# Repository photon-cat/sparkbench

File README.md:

# SparkBench

**All-in-one hardware development platform powered by Claude Opus 4.6**

SparkBench combines what normally takes 5 separate tools into one browser-based workbench: a code editor, circuit simulator, MCU emulator, EDA/PCB designer, and an AI engineering partner — all working together so you can go from idea to tested hardware in minutes instead of days.

## What It Does

- **Prompt-to-Circuit**: Describe what you want to build. Sparky (the AI agent) designs the schematic, writes the firmware, and presents a diff for your review.
- **Cycle-Accurate Simulation**: Run your Arduino code on an AVR emulator with 13+ simulated components (LEDs, servos, encoders, displays, sensors, shift registers).
- **KiCAD-Compatible PCB Editor**: Our custom-built PCB editor reads and writes native `.kicad_pcb` files. Built as a fork of KiCanvas with a full editing layer — component drag-and-drop, footprint rotation/flip, board outline editing (rectangle or SVG import), interactive trace routing, zone drawing, layer management, ratsnest display, courtyard DRC, undo/redo, and a 3D board preview. Everything stays in the KiCAD s-expression format so you can open your boards directly in KiCAD.
- **DeepPCB Autorouter Integration**: One-click AI-powered autorouting via [DeepPCB](https://deeppcb.ai). Send your board to DeepPCB's cloud autorouter directly from the PCB editor or let Sparky handle it conversationally. Extracts constraints, validates, runs placement and routing, and pulls back the routed board — all streamed with live progress.
- **Headless CI Testing**: Write YAML test scenarios and run them against the simulator — no hardware needed. AI-powered fuzz testing presses all the buttons and reports what broke.
- **Full-Context AI Agent**: Sparky has access to your entire project (schematic, code, PCB, libraries) and can debug, refactor, add features, route your PCB, or explain your circuit.

## Tech Stack

- **Frontend**: Next.js 16, React 19, Monaco Editor, Three.js (3D PCB viewer)
- **Simulation**: [avr8js](https://github.com/niclas-niclas/avr8js) (AVR emulator), [@wokwi/elements](https://github.com/niclas-niclas/wokwi-elements) (component visuals)
- **PCB Editor**: Custom KiCanvas fork with full editing — reads/writes `.kicad_pcb` s-expression format natively. Clipper2 for polygon math, WebGL2 rendering.
- **Autorouter**: [DeepPCB](https://deeppcb.ai) MCP integration — AI-powered PCB routing via SSE transport
- **AI**: Claude Opus 4.6 via [@anthropic-ai/claude-agent-sdk](https://www.npmjs.com/package/@anthropic-ai/claude-agent-sdk), custom MCP server for simulation control, DeepPCB MCP server for autorouting
- **Build**: PlatformIO (AVR compilation), runs entirely in the browser except compilation

## Architecture

```
┌─────────────────────────────────────────────────────────────┐
│  SparkBench Web                                             │
│  ┌──────────┐  ┌──────────────┐  ┌───────────────────────┐  │
│  │  Monaco   │  │  Diagram     │  │  Sparky Chat          │  │
│  │  Editor   │  │  Canvas      │  │  (Claude Opus 4.6)    │  │
│  │          │  │  + Wires     │  │  Agent SDK + MCP      │  │
│  └──────────┘  └──────────────┘  └───────────────────────┘  │
│  ┌──────────┐  ┌──────────────┐  ┌───────────────────────┐  │
│  │  Serial   │  │  PCB Editor  │  │  3D Board Viewer      │  │
│  │  Monitor  │  │  (KiCanvas   │  │  (Three.js)           │  │
│  │          │  │   fork)      │  │                       │  │
│  └──────────┘  └──────────────┘  └───────────────────────┘  │
│                                                             │
│  ┌─────────────────────────────────────────────────────────┐│
│  │  AVR Simulation Engine                                  ││
│  │  avr8js + I2C bus + SPI + USART + ADC + Timer/PWM      ││
│  │  Wire components: LED, servo, encoder, SSD1306, ...     ││
│  └─────────────────────────────────────────────────────────┘│
│                                                             │
│  ┌─────────────────────────────────────────────────────────┐│
│  │  DeepPCB Autorouter (via MCP SSE)                       ││
│  │  Extract constraints → Validate → Place → Route → Done  ││
│  └─────────────────────────────────────────────────────────┘│
└─────────────────────────────────────────────────────────────┘

┌─────────────────────────────────────────────────────────────┐
│  SparkBench CI                                              │
│  YAML scenarios → PlatformIO compile → headless AVR sim     │
│  set-control, wait-serial, expect-serial, expect-display    │
└─────────────────────────────────────────────────────────────┘
```

## PCB Editor

The PCB editor is a custom-built KiCAD-compatible editor, not a wrapper around existing tools. It reads and writes `.kicad_pcb` files natively using our own s-expression parser/serializer.

### Features

- **Component placement** — Click-to-select via pad proximity, drag with crosshair preview, grid snapping (0.5mm)
- **Footprint editing** — Rotate (R), flip front/back copper (F), delete, courtyard overlap detection
- **Board outline** — Set rectangle dimensions or upload custom SVG outlines, converted to KiCAD Edge.Cuts
- **Trace routing** — Interactive routing with orthogonal and 45° diagonal modes, via insertion, layer switching
- **Zone drawing** — Copper pour zones with net auto-detection from pad clicks
- **Layer management** — Full KiCAD layer stack (F.Cu, B.Cu, silkscreen, masks, etc.) with visibility toggles and highlighting
- **Ratsnest** — Displays unrouted connections as airline wires
- **Undo/redo** — 50-level snapshot-based undo stack
- **3D preview** — Three.js-based 3D board viewer with component models
- **Export** — Download `.kicad_pcb` files that open directly in KiCAD

### DeepPCB Autorouter

The PCB editor integrates with [DeepPCB](https://deeppcb.ai) for AI-powered autorouting. Two ways to use it:

**From the UI:** Click "Route with DeepPCB" in the PCB editor's right panel. The board is sent to DeepPCB's cloud autorouter, progress streams back in real-time, and the routed board is loaded back into the editor automatically.

**From Sparky:** Ask the AI agent to route your board (e.g., "route my PCB with DeepPCB"). Sparky uses DeepPCB's MCP tools directly — extracting constraints, validating, running placement/routing, and saving the result.

The autorouter workflow:
1. **Extract constraints** from the `.kicad_pcb` file
2. **Validate constraints** for correctness
3. **Run placement** — AI-optimized component positioning
4. **Run routing** — AI-powered trace routing
5. **Monitor progress** — live status updates streamed to the UI
6. **Retrieve result** — best routed board saved back to the project

## Getting Started

### Prerequisites

- Node.js 20+
- [PlatformIO Core](https://docs.platformio.org/en/latest/core/installation.html) (for compilation)
- Anthropic API key (for Sparky agent)
- DeepPCB API key (optional, for autorouting)

### Setup

```bash
git clone https://github.com/photon-cat/sparkbench.git
cd sparkbench
npm install
cp .env.example .env.local
# Edit .env.local with your keys:
#   ANTHROPIC_API_KEY=sk-ant-...
#   DEEPPCB_API_KEY=...          (optional, enables autorouter)
npm run dev
```

Open [http://localhost:3000](http://localhost:3000) to start building.

### SparkBench CLI

SparkBench includes a command-line tool for running tests and AI-powered security fuzzing directly from your terminal.

```bash
# Run it via npm
npm run sparkbench -- help

# Or directly with tsx
npx tsx scripts/sparkbench-cli.ts help
```

#### Commands

```
sparkbench test <project> [--scenario <file>]   Run a YAML test scenario
sparkbench fuzz <project>                       AI security fuzzer (SparkyFuzzer)
sparkbench list                                 List all projects
sparkbench help                                 Show help
```

#### Running Tests

Compile firmware with PlatformIO, then run a YAML test scenario against the headless AVR simulator:

```bash
npm run sparkbench -- test combo-safe
```

Test scenarios support: `delay`, `set-control` (buttons, encoders, pots, sensors), `send-serial`, `wait-serial`, `expect-serial`, `expect-display`, and `clear-serial`.

#### SparkyFuzzer (AI Security Auditor)

SparkyFuzzer uses Claude Opus 4.6 to analyze your firmware source code, identify security vulnerabilities, and generate exploit scenarios that run against the headless simulator to prove exploitability.

```bash
# Set your API key
export ANTHROPIC_API_KEY=sk-ant-...

# Fuzz the combo-safe demo (has 3 intentional vulnerabilities)
npm run sparkbench -- fuzz combo-safe
```

The fuzzer:
1. Sends your `sketch.ino` and `diagram.json` to Claude Opus 4.6
2. Claude identifies potential vulnerabilities (timing side-channels, integer overflows, backdoors, buffer overflows, etc.)
3. Claude generates YAML test scenarios that exploit each vulnerability
4. SparkBench runs each scenario headlessly against the AVR simulator
5. Claude analyzes the results and writes a security report

Reports are saved to `projects/<slug>/fuzzer-report/`.

## Simulated Components

| Component | Simulation |
|-----------|-----------|
| LED | GPIO state → visual on/off |
| Pushbutton | INPUT_PULLUP, interactive click |
| Potentiometer | ADC voltage via slider |
| Servo | PWM pulse width → angle display |
| Rotary Encoder (KY-040) | Quadrature CLK/DT signals |
| SSD1306 OLED | Full I2C controller, pixel display |
| 74HC595 | Serial-in/parallel-out, daisy chain |
| 74HC165 | Parallel-in/serial-out |
| DHT22 | One-wire temp/humidity with sliders |
| MPU6050 | I2C accel/gyro with sliders |
| 7-Segment Display | Via HC595 outputs |
| Buzzer | GPIO state detection |
| Slide Switch | Toggle state |

## Project Structure

```
sparkbench/
├── app/                    # Next.js app router
│   ├── api/chat/           # Sparky agent endpoint (Agent SDK)
│   ├── api/deeppcb/        # DeepPCB autorouter endpoint
│   ├── api/projects/       # Project CRUD + build API
│   └── projects/[slug]/    # Workbench page
├── components/             # React components
│   ├── DiagramCanvas.tsx   # Schematic editor with wiring
│   ├── SparkyChat.tsx      # AI chat panel with diff review
│   ├── KiPCBEditor.tsx     # PCB editor (KiCanvas fork)
│   ├── KiPCBCanvas.tsx     # WebGL2 board renderer
│   ├── KiPCBToolPalette.tsx # PCB tool sidebar
│   ├── KiPCBLayerPanel.tsx # Layer visibility/selection
│   ├── PCB3DViewer.tsx     # 3D board viewer (Three.js)
│   └── SimulationPanel.tsx # Simulation controls + tabs
├── hooks/                  # React hooks
│   ├── useKiPCBDrag.ts     # Footprint drag + courtyard DRC
│   ├── useKiPCBRouting.ts  # Interactive trace routing
│   ├── useKiPCBZoneDraw.ts # Copper zone drawing
│   └── useKiPCBBoardOutline.ts # Board outline editing
├── lib/                    # Core logic
│   ├── avr-runner.ts       # AVR emulator wrapper
│   ├── wire-components.ts  # Part simulation bindings
│   ├── scenario-runner.ts  # CI test runner
│   ├── sexpr-mutate.ts     # KiCAD s-expression tree manipulation
│   ├── sexpr-serializer.ts # S-expression → .kicad_pcb text
│   ├── deeppcb-client.ts   # DeepPCB MCP client wrapper
│   ├── pcb-parser.ts       # Schematic → PCB conversion
│   └── sparky-prompts.ts   # Sparky system prompt
├── vendor/kicanvas/        # KiCanvas fork (WebGL2 PCB renderer)
├── scripts/
│   ├── sparkbench-cli.ts   # CLI entry point (sparkbench command)
│   ├── run-scenario.ts     # Headless test runner
│   └── sparky-fuzzer.ts    # AI security fuzzer (SparkyFuzzer)
├── projects/               # User projects (diagram.json + sketch.ino)
└── _build/                 # PlatformIO build directory
```

## Hackathon Track

**Problem Statement Two: Break the Barriers** — Hardware development requires expensive tools (Altium, oscilloscopes), deep expertise (PCB layout, embedded C), and physical prototyping cycles. SparkBench puts the full hardware development workflow in everyone's hands with an AI partner that understands embedded systems.

## Built With

Built entirely during the [Claude Code Hackathon](https://cv.inc/e/claude-code-hackathon) using Claude Opus 4.6 and Claude Code.

## Team

- **photoncat** (Jacob Armstrong)

## License

MIT

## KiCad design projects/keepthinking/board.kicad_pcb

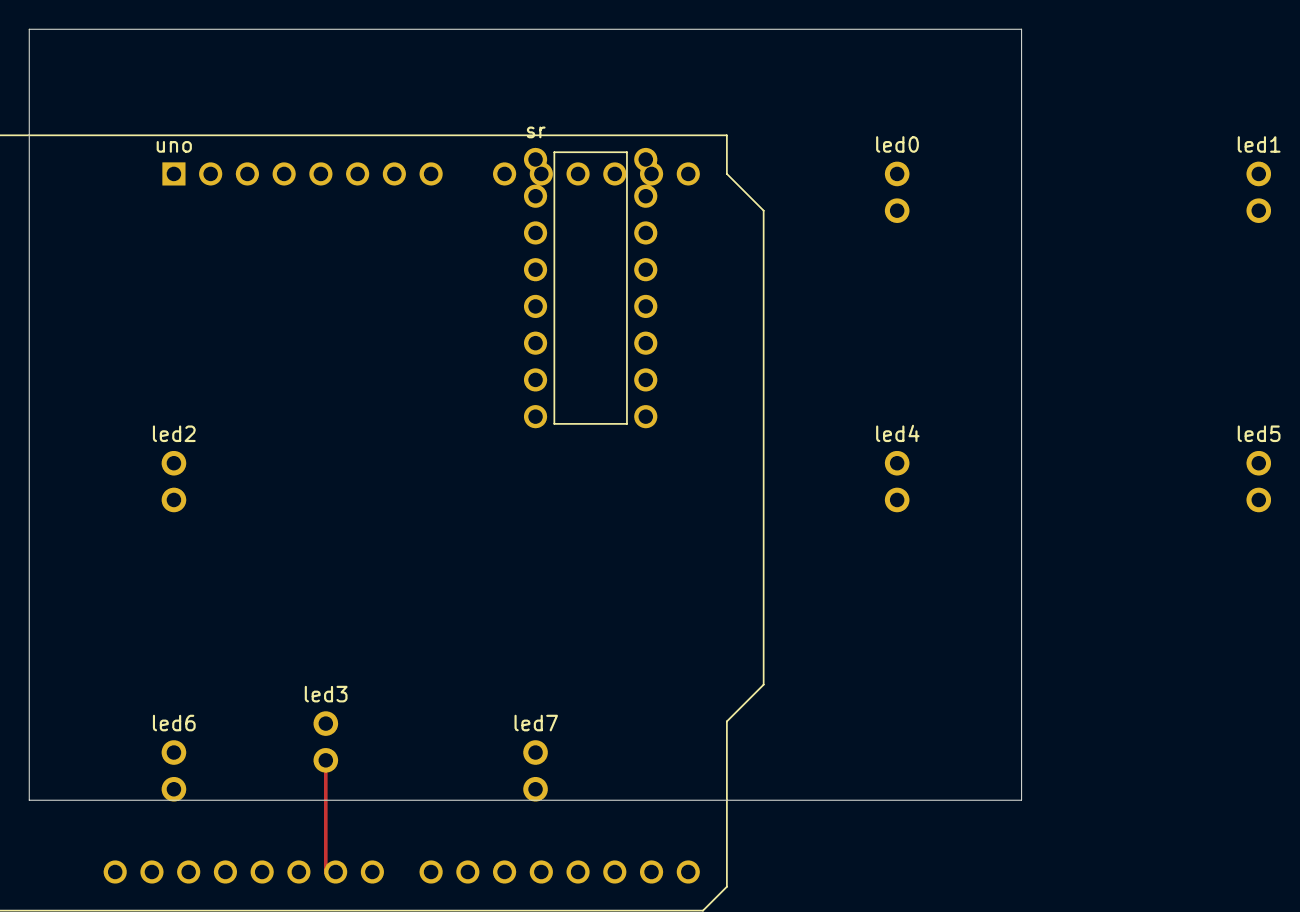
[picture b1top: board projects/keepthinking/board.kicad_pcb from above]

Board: 2 copper layers, 68.6 x 53.3 mm, 10 parts (0 on the bottom side), 15 nets.

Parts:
led0, led1, led2, led3, led4, led5, led6, led7: LED-THT-3mm
sr: DIP-16
uno: Arduino-Uno-Shield

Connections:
Net-1: sr.sr:14, uno.uno:4
Net-2: sr.sr:11, uno.uno:3
Net-3: sr.sr:12, uno.uno:2
Net-4: sr.sr:10, sr.sr:16, uno.uno:5V
Net-5: sr.sr:8, sr.sr:13, uno.uno:GND.1
Net-6: led0.led0:1, sr.sr:15
Net-7: led1.led1:1, sr.sr:1
Net-8: led2.led2:1, sr.sr:2
Net-9: led3.led3:1, sr.sr:3
Net-10: led4.led4:1, sr.sr:4
Net-11: led5.led5:1, sr.sr:5
Net-12: led6.led6:1, sr.sr:6
Net-13: led7.led7:1, sr.sr:7
Net-14: led0.led0:2, led1.led1:2, led2.led2:2, led3.led3:2, uno.uno:GND.2
Net-15: led4.led4:2, led5.led5:2, led6.led6:2, led7.led7:2, uno.uno:GND.3

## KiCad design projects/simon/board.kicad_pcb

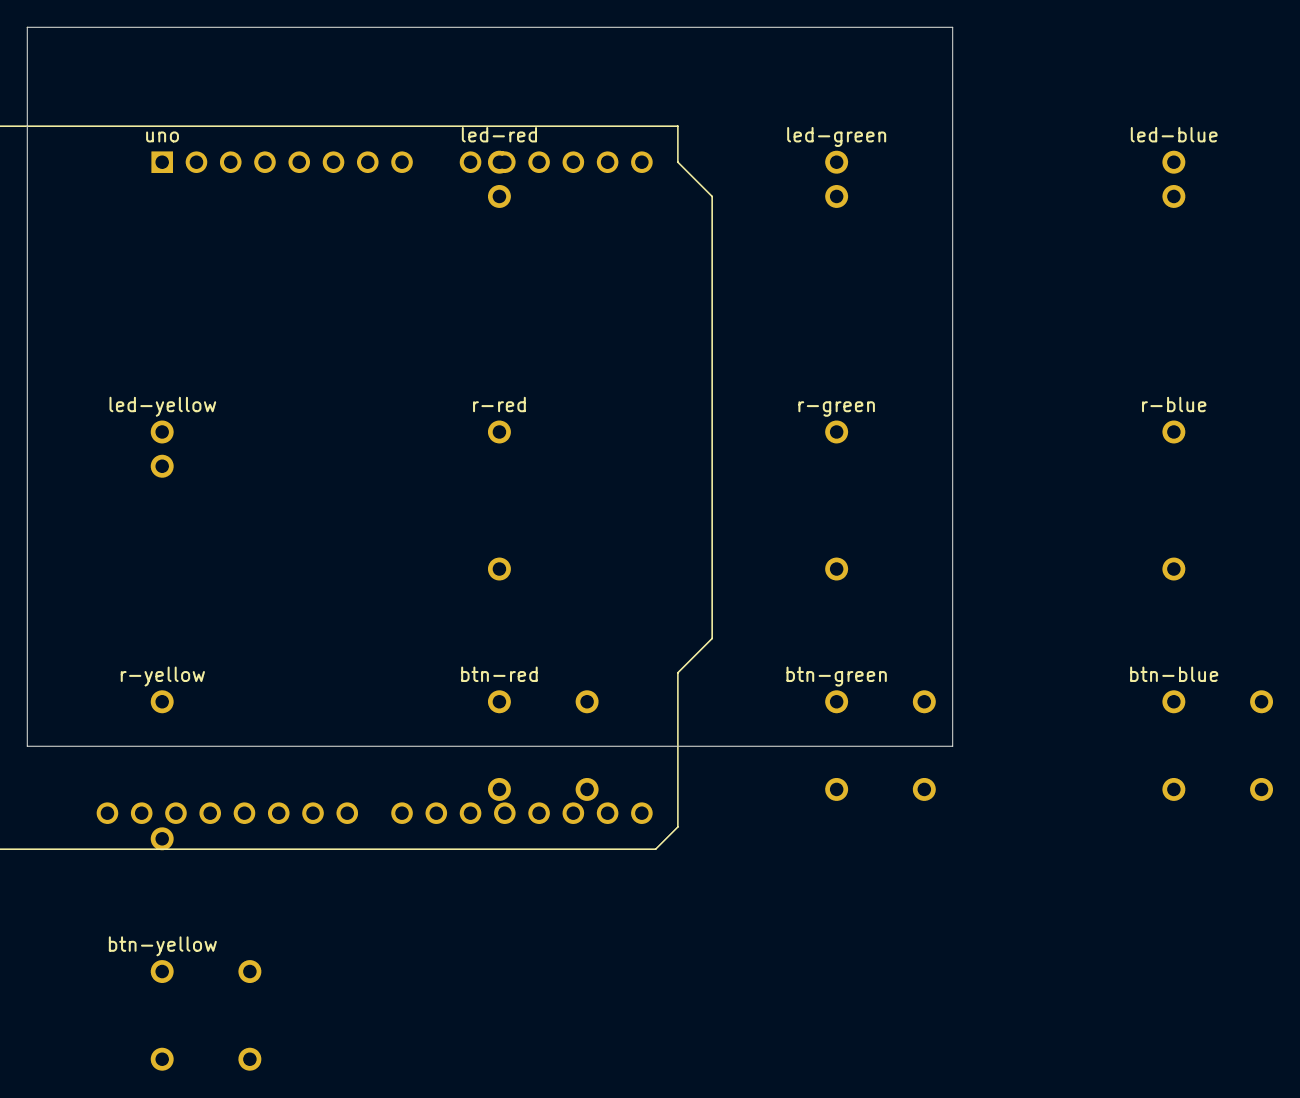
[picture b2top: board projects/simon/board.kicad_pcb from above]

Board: 2 copper layers, 68.6 x 53.3 mm, 13 parts (0 on the bottom side), 14 nets, no tracks yet.

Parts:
btn-blue: SW-THT-6mm
btn-green: SW-THT-6mm
btn-red: SW-THT-6mm
btn-yellow: SW-THT-6mm
led-blue: LED-THT-3mm
led-green: LED-THT-3mm
led-red: LED-THT-3mm
led-yellow: LED-THT-3mm
r-blue: 220; Axial-0.4in
r-green: 220; Axial-0.4in
r-red: 220; Axial-0.4in
r-yellow: 220; Axial-0.4in
uno: Arduino-Uno-Shield

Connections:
Net-1: r-red.r-red:1, uno.uno:12
Net-2: led-red.led-red:1, r-red.r-red:2
Net-3: btn-green.btn-green:1, btn-red.btn-red:1, led-green.led-green:2, led-red.led-red:2, uno.uno:GND.1
Net-4: r-green.r-green:1, uno.uno:11
Net-5: led-green.led-green:1, r-green.r-green:2
Net-6: r-blue.r-blue:1, uno.uno:10
Net-7: led-blue.led-blue:1, r-blue.r-blue:2
Net-8: btn-blue.btn-blue:4, btn-yellow.btn-yellow:4, led-blue.led-blue:2, led-yellow.led-yellow:2, uno.uno:GND.2
Net-9: r-yellow.r-yellow:1, uno.uno:9
Net-10: led-yellow.led-yellow:1, r-yellow.r-yellow:2
Net-11: btn-red.btn-red:4, uno.uno:5
Net-12: btn-green.btn-green:4, uno.uno:4
Net-13: btn-blue.btn-blue:1, uno.uno:3
Net-14: btn-yellow.btn-yellow:1, uno.uno:2

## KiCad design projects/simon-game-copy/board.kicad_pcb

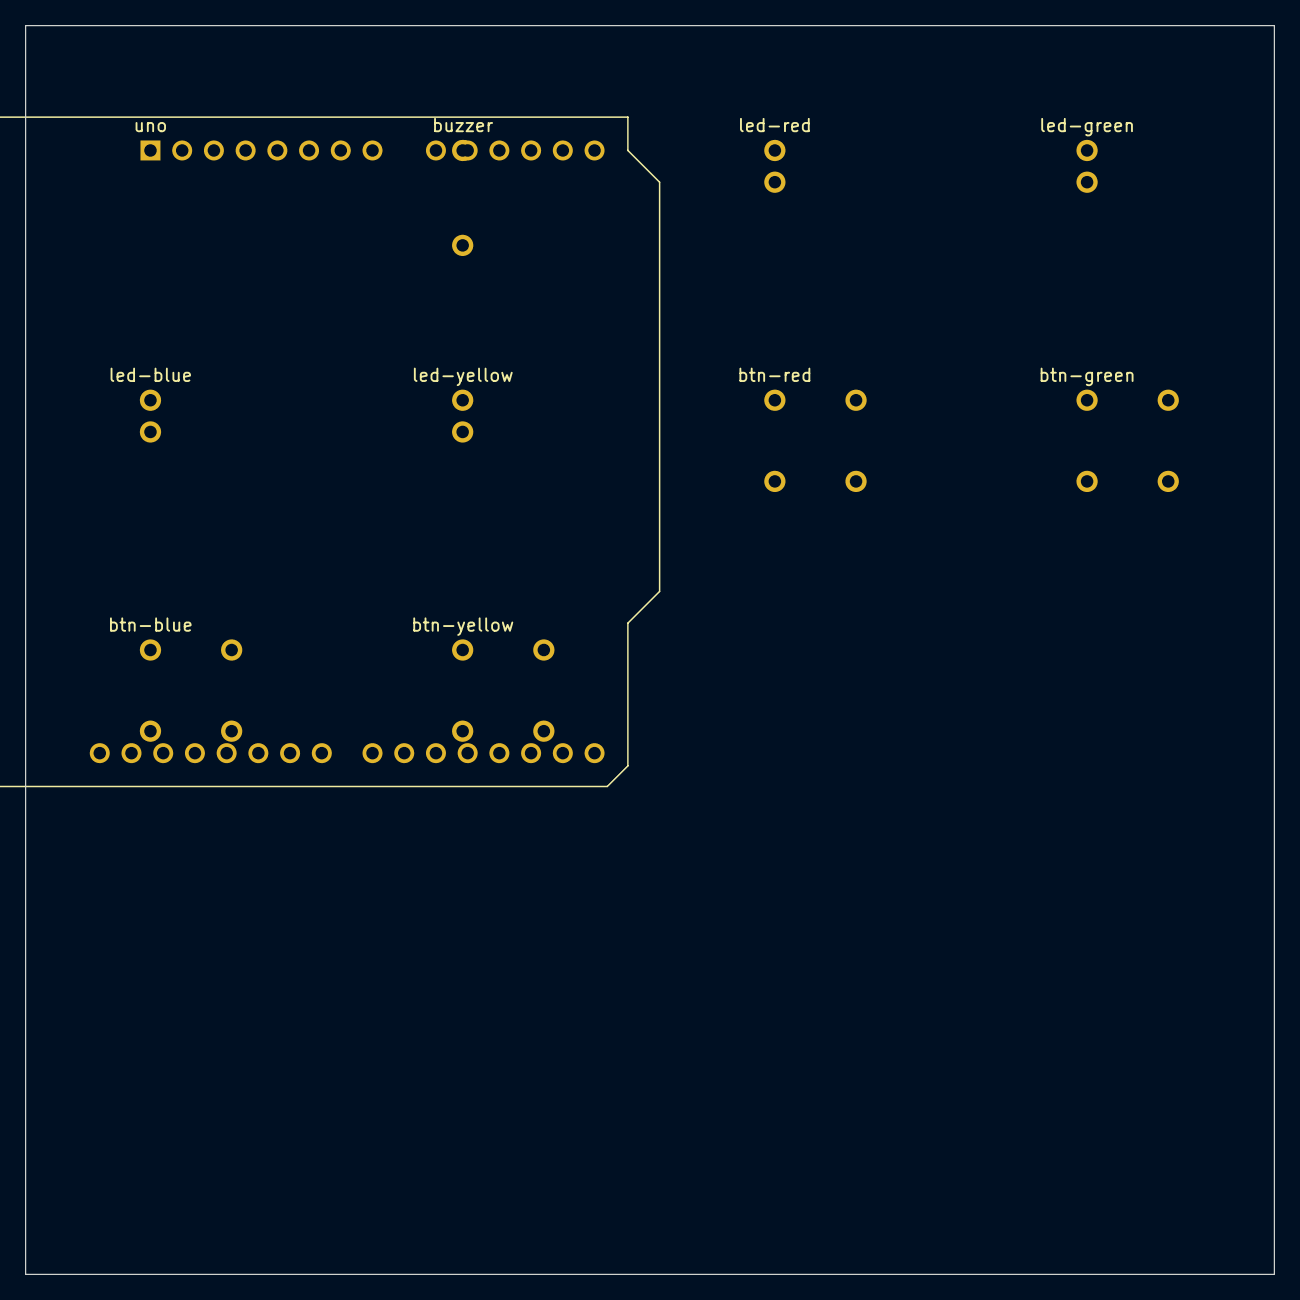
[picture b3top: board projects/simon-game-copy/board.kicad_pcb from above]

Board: 2 copper layers, 100.0 x 100.0 mm, 10 parts (0 on the bottom side), 10 nets, no tracks yet.

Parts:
btn-blue: SW-THT-6mm
btn-green: SW-THT-6mm
btn-red: SW-THT-6mm
btn-yellow: SW-THT-6mm
buzzer: Buzzer-12mm
led-blue: LED-THT-3mm
led-green: LED-THT-3mm
led-red: LED-THT-3mm
led-yellow: LED-THT-3mm
uno: Arduino-Uno-Shield

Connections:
Net-1: btn-blue.btn-blue:4, btn-green.btn-green:1, btn-red.btn-red:1, btn-yellow.btn-yellow:4, buzzer.buzzer:1, led-blue.led-blue:2, led-green.led-green:2, led-red.led-red:2, led-yellow.led-yellow:2, uno.uno:GND.1
Net-2: btn-yellow.btn-yellow:1, uno.uno:2
Net-3: btn-blue.btn-blue:1, uno.uno:3
Net-4: btn-green.btn-green:4, uno.uno:4
Net-5: btn-red.btn-red:4, uno.uno:5
Net-6: buzzer.buzzer:2, uno.uno:8
Net-7: led-yellow.led-yellow:1, uno.uno:9
Net-8: led-blue.led-blue:1, uno.uno:10
Net-9: led-green.led-green:1, uno.uno:11
Net-10: led-red.led-red:1, uno.uno:12

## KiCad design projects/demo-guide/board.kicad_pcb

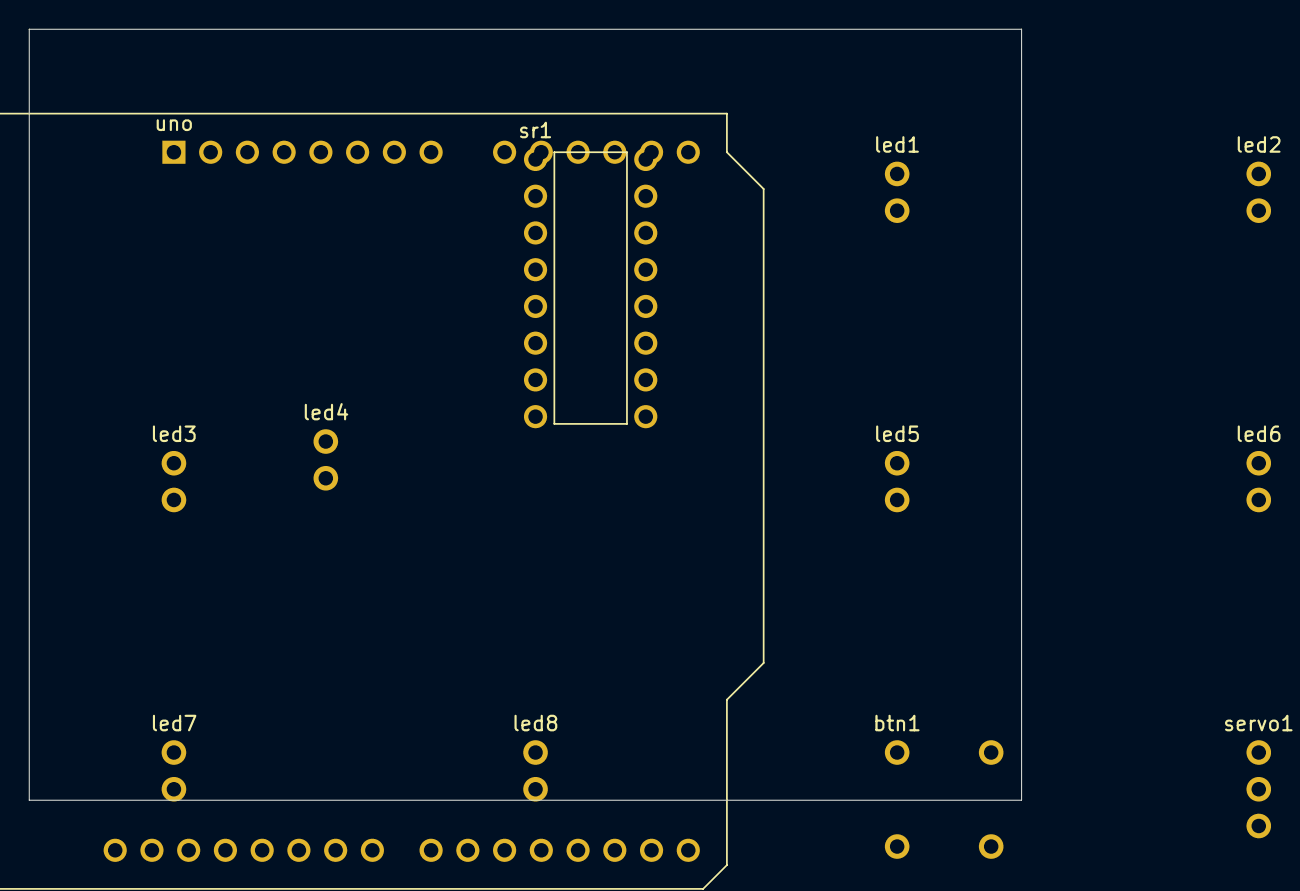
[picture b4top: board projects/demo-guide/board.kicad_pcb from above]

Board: 2 copper layers, 68.6 x 53.3 mm, 12 parts (0 on the bottom side), 17 nets, no tracks yet.

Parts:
btn1: SW-THT-6mm
led1, led2, led3, led4, led5, led6, led7, led8: LED-THT-3mm
servo1: Header-1x3
sr1: DIP-16
uno: Arduino-Uno-Shield

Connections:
Net-1: sr1.sr1:14, uno.uno:2
Net-2: sr1.sr1:11, uno.uno:3
Net-3: sr1.sr1:12, uno.uno:4
Net-4: servo1.servo1:2, sr1.sr1:16, uno.uno:5V
Net-5: led1.led1:2, led2.led2:2, led3.led3:2, led4.led4:2, led5.led5:2, led6.led6:2, led7.led7:2, led8.led8:2, sr1.sr1:8, sr1.sr1:13, uno.uno:GND.1
Net-6: led1.led1:1, sr1.sr1:15
Net-7: led2.led2:1, sr1.sr1:1
Net-8: led3.led3:1, sr1.sr1:2
Net-9: led4.led4:1, sr1.sr1:3
Net-10: led5.led5:1, sr1.sr1:4
Net-11: led6.led6:1, sr1.sr1:5
Net-12: led7.led7:1, sr1.sr1:6
Net-13: led8.led8:1, sr1.sr1:7
Net-14: btn1.btn1:4, uno.uno:5
Net-15: btn1.btn1:1, uno.uno:GND.2
Net-17: servo1.servo1:1, uno.uno:GND.3
Net-18: servo1.servo1:3, uno.uno:9

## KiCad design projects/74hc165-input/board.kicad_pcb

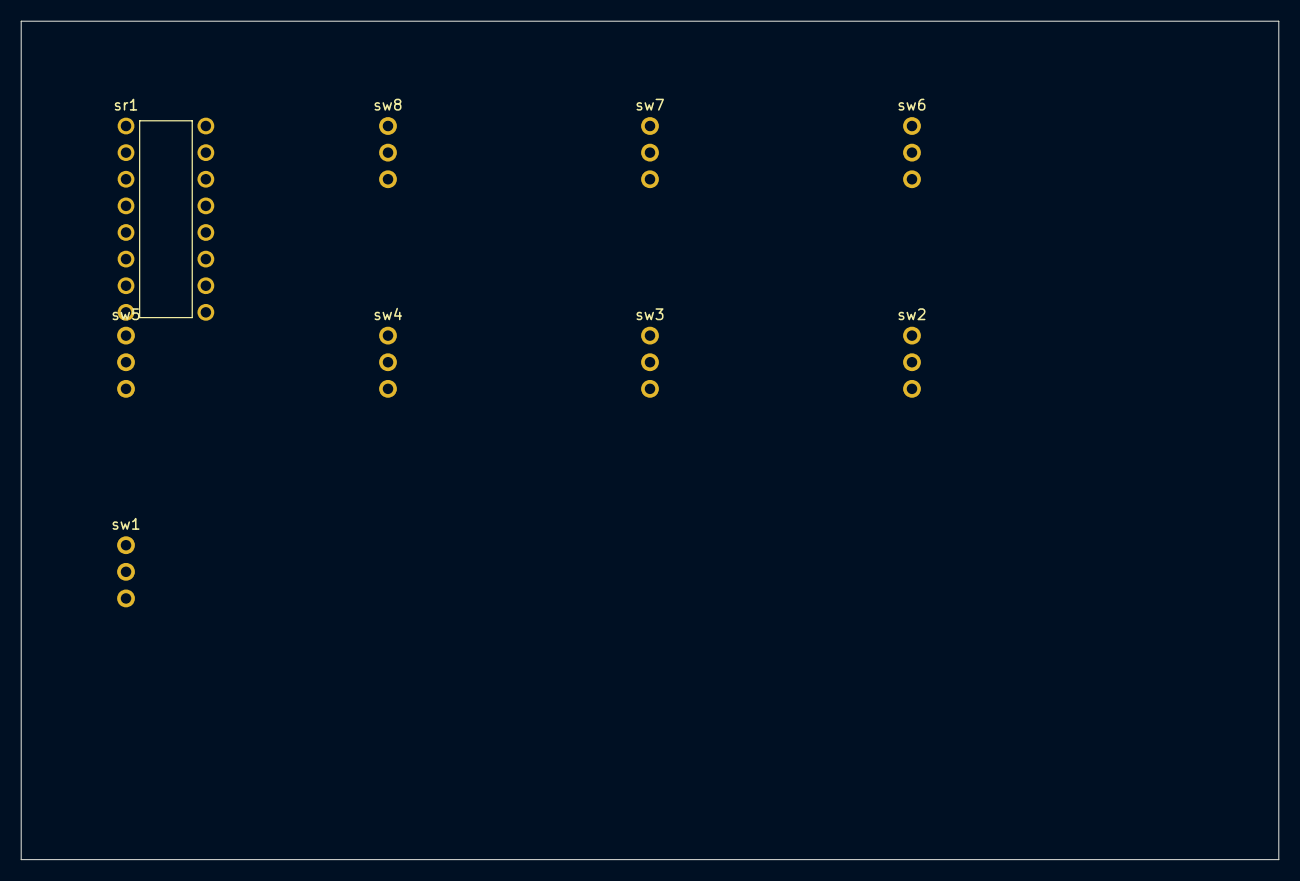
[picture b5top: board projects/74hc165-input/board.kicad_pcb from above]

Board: 2 copper layers, 120.0 x 80.0 mm, 9 parts (0 on the bottom side), 2 nets, no tracks yet.

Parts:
sr1: DIP-16
sw1, sw2, sw3, sw5, sw6, sw7, sw8: SW-SPDT-THT
sw4: Header-1x03

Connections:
Net-12: sw1.sw1:1, sw2.sw2:1, sw3.sw3:1, sw4.sw4:1, sw5.sw5:1, sw6.sw6:1, sw7.sw7:1, sw8.sw8:1
Net-13: sw1.sw1:3, sw2.sw2:3, sw3.sw3:3, sw4.sw4:3, sw5.sw5:3, sw6.sw6:3, sw7.sw7:3, sw8.sw8:3

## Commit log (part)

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2026-02-14 "Claude Code Review workflow"
2026-02-14 "Claude PR Assistant workflow"
